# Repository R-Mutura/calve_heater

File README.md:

# CALVE HEATER
This product features 3 main parts: the fabric containig a heater and  temperature RTD sensor embedded in it, a PCB that runs the heater and warming process and Firmware that is burnt in to the MCU located on the PCB assembly. 
The product features a modular approach where the controlling PCB can be plugged and unplugged from the fabric at will. It has a small form factor that allows it to be a hand held device that is powered via a Li-Po battery.

### How it works 🔧
THe PCB contains JST connectors from where the heater and temperature sensor are plugged into the board. Make sure thwy are plugged in. Press the ON button(left od USB) and the device wakes up and starsts the heating process. To turn off the device, Long press the ON button for about 1 sec. This will cause the device to go to sleep.
Temperature level setting is achieved via the use of the temperature button. (Button right of the USB). Default setting is at 40 degrees. Pressing it once increases the level to 44 deg, pressing it once again increases the level to 48 deg. Once at the highest level pressing the button again will take the level back to the initial  40 deg. The temperature level is indicated by use of the LED below the temperature button. 

- Green = 40deg
- Blue = 44deg
- Red = 48deg
<br>
The device uses PID control to warm up the fabric and maintain the desired temperature at all times ensuring safe.bumpless and comfortable use.
When the battery level gets too low the RED led flashes at 1 sec intervals indicating need for charging. 
the device is charged via the Micro-USB port. During charging, 2 leds below the on button are used for monitoring. Red is constantly on if its connected to power, and the Green LED indicates charging status:
- ON = CHarging
- OFF = Done charging <br>
<br>

# HARDWARE COMPONENTS
Heater [link](https://www.alibaba.com/product-detail/High-Temperature-Flexible-Ployimide-PI-Film_60627303766.html)   [link2](https://www.alibaba.com/product-detail/Thermostatic-electric-carbon-fiber-heating-element_62302051301.html?spm=a2700.wholesale.0.0.c5e0bc1cLrvEdd) <br>
Battery [link](https://www.indiamart.com/proddetail/lithium-ion-batteries-3-7v-2500mah-10433305048.html)  <br>
RTD sensor [link](https://www.digikey.com/en/products/detail/te-connectivity-measurement-specialties/R-8203/5277360)<br>
<br>
For the PCB components refer to the BOM folder in the hardware section.

# SAFETY
All the electrical components are on the PCB and can be disconnected in case of any critical situations by the user. Ensure to keep the device free from water and dust that may block the connectors. Disconnect the PCB device when washing the fabric. The Heater is a well made material wwith insulated wires to avoid shocking the user in amy way. When washing ensure not to cut, scrape or peel off any parts. Consider best practices [link](https://www.youtube.com/watch?v=5kIUcR_C9-A)

# BURNING BOOTLOADER AND FIRMWARE TO THE PCB
### Download the Files :arrow_down_small:
From this repo click on the download option at the code :arrow_double_down: 
- You will have two folders inside the main folder i.e 📁 Bootloader and  📁calve_heater_furmware
<br>
##  Burning bootload to the MCU :fire:
 <h3> Note: 
 DO THIS ON A WINDOWS OPERATING SYSTEM!!!
  </h3>
1) To do this you will need an older version of the arduino particularly version 1.6.9 find it here :link: [Old SoftwareReleases Arduino IDE](https://www.arduino.cc/en/main/OldSoftwareReleases) <br/>
2) Once you have it setup to burn the bootloader follow this tutotial keenly:link: [Burning Arduino Bootloader](https://create.arduino.cc/projecthub/techmirtz/arduino-without-external-clock-crystal-on-atmega328-d4fcc4) <br>
3) You can also use a USBASP to burn the bootloader. Note the above instruction will be used but instead of selecting arduino as ISP your programmer the USBASP is selected. 

[buy usbasp](https://aliexpress.ru/af/USBASP-USBISP-AVR-Programmer-USB.html?catId=0&d=y&aff_platform=portals-tool&initiative_id=SB_20201020044645&origin=n&sk=_9JHld5&aff_trace_key=4b1704d992da43b586041dfb7cd31d7e-1606574782769-00350-_9JHld5&SearchText=USBASP%2BUSBISP%2BAVR%2BProgrammer%2BUSB&terminal_id=351d58321dfa473cb106b58978d7c19c)
or here 
 :link: [buy usbasp](https://aliexpress.ru/item/32649685244.html?spm=a2g0o.productlist.0.0.22e26eaf2mIeLt&algo_pvid=b6506204-320d-4244-9d76-c7a1c32c5ee5&algo_expid=b6506204-320d-4244-9d76-c7a1c32c5ee5-16&btsid=0b8b036a16065747853274219e2939&ws_ab_test=searchweb0_0,searchweb201602_,searchweb201603_)
 <br/>
 
 ## Uploading the codes  :arrow_up:
 1) Open the 📁calve_heater_furmware Folder and open the INO file with your arduino
2) If you use Arduino as your programmer or an FTDI, Follow the instructions here from step 3: [Uploading Code](https://create.arduino.cc/projecthub/techmirtz/arduino-without-external-clock-crystal-on-atmega328-d4fcc4)
3) However if you are using a USBASP, Follow the following instructions:<br>
   a) Insert the ISP programmer cable socket onto ISP header. ...<br>
   b) Open Arduino IDE software. ...<br>
   c) Next, call out any example of source code. ...<br>
   d) Select “USBasp” from the Tools > Programmer menu.<br>
   e) Select “Upload using Programmer” from the File menu.<br>
 You can also explore more from the following tutorial :link:[How to Use USBasp Programmer with Arduino Boards](https://www.youtube.com/watch?v=ToKerwRR-70)

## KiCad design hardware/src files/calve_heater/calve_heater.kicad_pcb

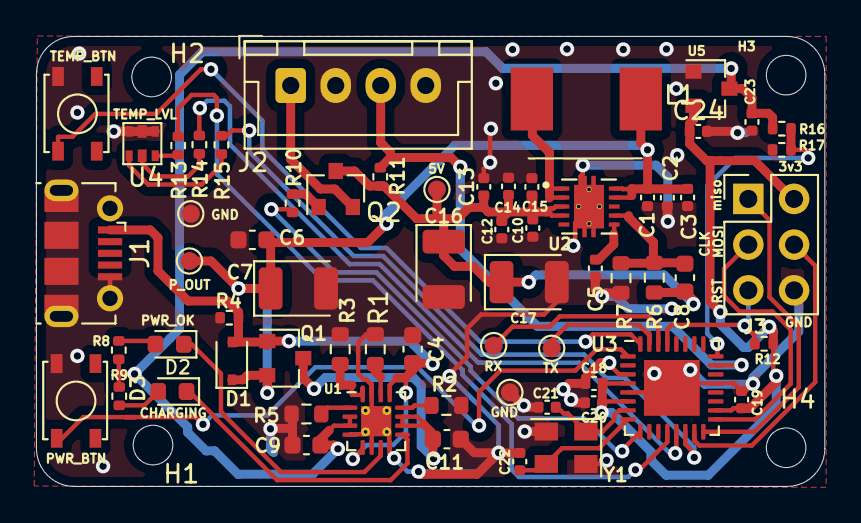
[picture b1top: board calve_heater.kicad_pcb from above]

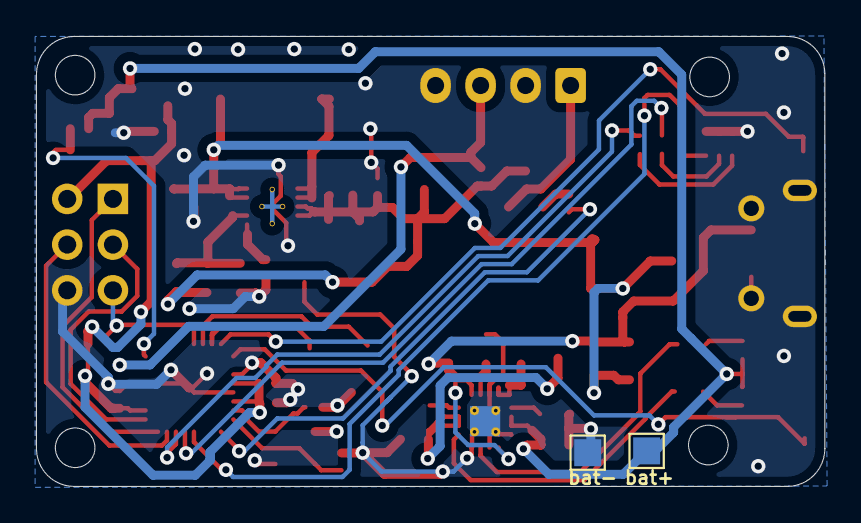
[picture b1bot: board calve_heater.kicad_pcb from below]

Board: 2 copper layers, 43.8 x 25.0 mm, 70 parts (2 on the bottom side), 39 nets.

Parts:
5V: TestPoint; TestPoint_Pad_D1.0mm
C1, C2, C3, C23, C24: 10u; C_0402_1005Metric
C4: 1u; C_0603_1608Metric
C5: 10n; C_0402_1005Metric
C6: 4.7u; C_0603_1608Metric
C7, C16, C17: 100u; CP_EIA-3528-21_Kemet-B
C8: 18p; C_0603_1608Metric
C9, C11: 10u; C_0603_1608Metric
C10, C12, C13, C14, C15: 4.7u; C_0402_1005Metric
C18, C19, C20: 100nF; C_0402_1005Metric
C21, C22: 22pF; C_0402_1005Metric
D1: D_Schottky_Small; D_SOD-323
D2: GREEN; LED_0603_1608Metric
D3: RED; LED_0603_1608Metric
GND: TestPoint; TestPoint_Pad_D1.0mm
GND#2: TestPoint; TestPoint_Pad_D1.0mm
H1, H2, H3, H4: MountingHole; MountingHole_2.2mm_M2_ISO14580
J1: USB_B_Micro; USB_Micro-B_Molex-105017-0001
J2: Conn_out; JST_XH_B4B-XH-A_1x04_P2.50mm_Vertical
J3: ICSP_HEADER; PinHeader_2x03_P2.54mm_Vertical
L1: 1.5uH; MWSA0518S-1R5MT
PWR_BTN: SW_Push; SKRPACE010
P_OUT: TestPoint; TestPoint_Pad_D1.0mm
Q1: FDN338P-NL; SOT-23
Q2: SI2304BDS-T1-GE3; SOT-23
R1: 50k; R_0603_1608Metric
R2: 1.07k; R_0603_1608Metric
R3: 750R; R_0603_1608Metric
R4: 10k; R_0402_1005Metric
R5: 10k; R_0603_1608Metric
R6: 402k; R_0603_1608Metric
R7: 100k; R_0603_1608Metric
R8, R9: 1k; R_0402_1005Metric
R10, R11: 150R; R_0402_1005Metric
R12: 4.7K; R_0402_1005Metric
R13, R14, R15, R16, R17: 1K; R_0402_1005Metric
RX: RX; TestPoint_Pad_D1.0mm
TEMP_BTN: SW_Push; SKRPACE010
TX: TX; TestPoint_Pad_D1.0mm
U1: BQ24075RGT; VQFN-16-1EP_3x3mm_P0.5mm_EP1.68x1.68mm_ThermalVias
U2: TPS61230DRCR; VREG_V62_16624-01YE
U3: ATmega328P-MU; QFN-32-1EP_5x5mm_P0.5mm_EP3.1x3.1mm
U4: EAST1616RGBA8
U5: LM1117-3.3; SOT-23
Y1: X322516MOB4SI; Crystal_SMD_EuroQuartz_MT-4Pin_3.2x2.5mm
bat+: TestPoint; TestPoint_Pad_1.5x1.5mm
bat-: TestPoint; TestPoint_Pad_1.5x1.5mm

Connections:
+3V3: C18.1, C19.1, C20.1, C24.1, J3.2, R12.1, U3.4, U3.6, U3.18, U5.2
+5V: 5V.1, C8.1, C10.1, C12.1, C13.1, C14.1, C15.1, C16.1, C17.1, Q2.3, R6.1, R11.2, U2.3, U2.4
/PWR_OUT: C1.1, C2.1, C3.1, C6.1, C7.1, D1.1, L1.1, P_OUT.1, Q1.2, U2.9, U2.10
/VBAT_OUT: C11.1, Q1.3, U1.10, U1.11
/controller/CLK: J3.3, U3.17
/controller/HEATER_+VE: J2.1, Q2.2
/controller/HEATER_PWM_PIN: R10.2, U3.9
/controller/LED_BLUE: R15.1, U3.14
/controller/LED_GREEN: R14.1, U3.13
/controller/LED_RED: R13.1, U3.12
/controller/MISO: J3.1, U3.16
/controller/MOSI: J3.4, U3.15
/controller/ON_OFF_BTN: PWR_BTN.1, U3.1
/controller/RTD_+VE: J2.3, R11.1, U3.23
/controller/RXD: RX.1, U3.30
/controller/TEMP_LVL_BTN: TEMP_BTN.1, U3.32
/controller/TXD: TX.1, U3.31
/controller/XTAL1: C21.1, U3.7, Y1.1
/controller/XTAL2: C22.1, U3.8, Y1.3
/controller/reset: J3.5, R12.2, U3.29
/~CHRG: D3.1, U1.9
/~PGOOD: D2.1, U1.7
GND: C1.2, C2.2, C3.2, C4.2, C5.2, C6.2, C7.2, C9.2, C10.2, C11.2, C12.2, C13.2, C14.2, C15.2, C16.2, C17.2, C18.2, C19.2, C20.2, C21.2, C22.2, C23.2, C24.2, GND.1, GND#2.1, J1.5, J1.6, J2.2, J2.4, J3.6, PWR_BTN.2, R1.2, R2.2, R3.2, R4.2, R5.2, R7.2, R17.2, TEMP_BTN.2, U1.4, U1.6, U1.8, U1.15, U1.17, U2.11, U3.3, U3.5, U3.21, U3.33, U4.2, U4.4, U4.6, U5.1, Y1.2, Y1.4, bat-.1
unnamed: C5.1, U2.6
unnamed: C8.2, R6.2, R7.1, U2.7
unnamed: D2.2, R8.2
unnamed: D3.2, R9.2
unnamed: L1.2, U2.1, U2.2
unnamed: Q2.1, R10.1
unnamed: R1.1, U1.14
unnamed: R2.1, U1.12
unnamed: R3.1, U1.16
unnamed: R5.1, U1.1
unnamed: R13.2, U4.1
unnamed: R14.2, U4.3
unnamed: R15.2, U4.5
unnamed: R16.2, R17.1, U3.24
VBUS: C4.1, D1.2, J1.1, Q1.1, R4.1, U1.5, U1.13
vbat+: C9.1, C23.1, R8.1, R9.1, R16.1, U1.2, U1.3, U5.3, bat+.1

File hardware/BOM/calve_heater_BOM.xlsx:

C1-C3, C23, C24 | 10u | Capacitor_SMD:C_0402_1005Metric |  |  | 6.3V | 5
C4 | 1u | Capacitor_SMD:C_0603_1608Metric |  |  | 16V | 1
C5 | 10n | Capacitor_SMD:C_0402_1005Metric |  |  | 6.3V | 1
C6 | 4.7u | Capacitor_SMD:C_0603_1608Metric |  |  | 10V | 1
C8 | 18p | Capacitor_SMD:C_0603_1608Metric |  |  | 50V | 1
C9, C11 | 10u | Capacitor_SMD:C_0603_1608Metric |  |  | 16V | 2
C10, C12-C15 | 4.7u | Capacitor_SMD:C_0402_1005Metric |  |  | 10V | 5
C7, C16, C17 | 100u | Capacitor_Tantalum_SMD:CP_EIA-3528-21_Kemet-B |  | VZT101M1VTR-0606 |  | 3
C18-C20 | 100nF | Capacitor_SMD:C_0402_1005Metric |  |  |  | 3
C21, C22 | 22pF | Capacitor_SMD:C_0402_1005Metric |  |  |  | 2
D1 | D_Schottky_Small | Diode_SMD:D_SOD-323 |  |  |  | 1
D2 | GREEN | LED_SMD:LED_0603_1608Metric |  |  |  | 1
D3 | RED | LED_SMD:LED_0603_1608Metric |  |  |  | 1
H1-H4 | MountingHole | MountingHole:MountingHole_2.2mm_M2_ISO14580 |  |  |  | 4
J1 | USB_B_Micro | Connector_USB:USB_Micro-B_Molex-105017-0001 |  |  |  | 1
J2 | Conn_out | Connector_JST:JST_XH_B4B-XH-A_1x04_P2.50mm_Vertical | S4B-XH-SM4-TB(LF)(SN) |  |  | 1
J3 | ICSP_HEADER | Connector_PinHeader_2.54mm:PinHeader_2x03_P2.54mm_Vertical |  |  |  | 1
L1 | 1.5uH | greencharge-footprints:MWSA0518S-1R5MT | MWSA0518S-1R5MT |  |  | 1
Q1 | FDN338P-NL | Package_TO_SOT_SMD:SOT-23 | FDN338P-NL |  |  | 1
Q2 | SI2304BDS-T1-GE3 | Package_TO_SOT_SMD:SOT-23 |  |  |  | 1
R1 | 50k | Resistor_SMD:R_0603_1608Metric |  |  |  | 1
R2 | 1.07k | Resistor_SMD:R_0603_1608Metric |  |  |  | 1
R3 | 750R | Resistor_SMD:R_0603_1608Metric |  |  |  | 1
R4 | 10k | Resistor_SMD:R_0402_1005Metric |  |  |  | 1
R5 | 10k | Resistor_SMD:R_0603_1608Metric |  |  |  | 1
R6 | 402k | Resistor_SMD:R_0603_1608Metric |  |  |  | 1
R7 | 100k | Resistor_SMD:R_0603_1608Metric |  |  |  | 1
R8, R9 | 1k | Resistor_SMD:R_0402_1005Metric |  |  |  | 2
R10, R11 | 150R | Resistor_SMD:R_0402_1005Metric |  |  |  | 2
R12 | 4.7K | Resistor_SMD:R_0402_1005Metric |  |  |  | 1
R13-R17 | 1K | Resistor_SMD:R_0402_1005Metric |  |  |  | 5
SW1, SW2 | SW_Push | greencharge-footprints:SKRPACE010 |  |  |  | 2
TP1, TP2 | TestPoint | TestPoint:TestPoint_Pad_1.5x1.5mm |  |  |  | 2
TP3-TP6 | TestPoint | TestPoint:TestPoint_Pad_D1.0mm |  |  |  | 4
TP7 | RX | TestPoint:TestPoint_Pad_D1.0mm |  |  |  | 1
TP8 | TX | TestPoint:TestPoint_Pad_D1.0mm |  |  |  | 1
U1 | BQ24075RGT | Package_DFN_QFN:VQFN-16-1EP_3x3mm_P0.5mm_EP1.68x1.68mm_ThermalVias |  |  |  | 1
U2 | TPS61230DRCR | greencharge-footprints:VREG_V62_16624-01YE | TPS61230DRCR |  |  | 1
U3 | ATmega328P-MU | Package_DFN_QFN:QFN-32-1EP_5x5mm_P0.5mm_EP3.1x3.1mm |  |  |  | 1
U4 | EAST1616RGBA8 | greencharge-footprints:EAST1616RGBA8 |  |  |  | 1
U5 | LM1117-3.3 | Package_TO_SOT_SMD:SOT-23 | LM1117GSF-3.3 |  |  | 1
Y1 | X322516MOB4SI | Crystal:Crystal_SMD_EuroQuartz_MT-4Pin_3.2x2.5mm |  |  |  | 1

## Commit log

2022-01-07 Update README.md
    updated readme documentation
2022-01-07 update on calve design
2022-01-07 updated bom
